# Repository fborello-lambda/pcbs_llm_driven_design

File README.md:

<div align="center">

# [pcbs_llm_driven_design](https://github.com/fborello-lambda/pcbs_llm_driven_design)

Four KiCad 10 hardware projects developed through an LLM-assisted design workflow.

Schematics · routed PCBs · readable BOMs · 3D previews · reproducible fabrication exports

</div>

| Board | Preview | Design files |
| --- | --- | --- |
| [220 Vac halogen dimmer](dimmer/) |  | [KiCad project](dimmer/esp32_dimmer.kicad_pro) · [schematic PDF](dimmer/docs/schematic.pdf) · [BOM](dimmer/docs/BOM.csv) |
| [BLE remote controller](remote_controller/) |  | [KiCad project](remote_controller/esp32c3_remote.kicad_pro) · [schematic PDF](remote_controller/docs/schematic.pdf) · [BOM](remote_controller/BOM.csv) |
| [Photodiode TIA laboratory](photodiode_lab/) |  | [KiCad project](photodiode_lab/photodiode_lab.kicad_pro) · [schematic PDF](photodiode_lab/docs/schematic.pdf) · [BOM](photodiode_lab/BOM.csv) |
| [Raspberry Pi SPI0 breakout](raspberry_spi0_breakout/) |  | [KiCad project](raspberry_spi0_breakout/raspberry_spi0_breakout.kicad_pro) · [schematic PDF](raspberry_spi0_breakout/docs/schematic.pdf) · [BOM](raspberry_spi0_breakout/BOM.csv) |

## Fabricated board photos

| Halogen dimmer | BLE remote controller | Photodiode TIA lab | Raspberry Pi SPI0 breakout |
| --- | --- | --- | --- |
|  |  |  |  |

## Repository layout

Each board has one self-contained project directory. Reusable ESP32-C3 symbol, footprint, and STEP assets live in `shared/`; deterministic generators and validation tools live in `scripts/`. Personal KiCad state, editor settings, caches, credentials, reports, and temporary files are excluded from version control.

The three ESP32 boards consume the same canonical ESP32-C3 SuperMini library. The Raspberry Pi board is an independent passive SPI0 adapter.

## Validation

Create the Python environment with access to KiCad's system-provided `pcbnew` module, then run the repository checks:

```sh
uv venv --python /usr/bin/python3 --system-site-packages
uv sync
uv run --no-sync python scripts/check_all.py
```

The check runs ERC, DRC, and schematic/PCB parity for all four projects. It also verifies the shared ESP32 footprint geometry and STEP reference on the three ESP32 boards.

Regenerate the committed documentation assets with:

```sh
uv run --no-sync python scripts/export_publishable_docs.py
```

## Fabrication ZIPs

Generate deterministic Gerber/drill ZIPs for all four boards with:

```sh
uv run --no-sync python scripts/export_fabrication.py
```

The ZIPs are written under each project's ignored `outputs/` directory. Publish tested ZIPs as GitHub Release assets so generated manufacturing files do not obscure source review or become stale in the main branch.

## Safety

These boards are engineering prototypes, not certified products. In particular, the dimmer switches 220 Vac and requires qualified review of creepage, clearance, insulation, fuse coordination, connector ratings, thermal performance, enclosure, EMC, and fabrication constraints before use. CAD checks do not establish electrical safety or the advertised load rating.

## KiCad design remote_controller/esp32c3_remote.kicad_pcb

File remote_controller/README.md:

# ESP32-C3 BLE dimmer remote — revision G

[KiCad project](esp32c3_remote.kicad_pro) · [Schematic PDF](docs/schematic.pdf) · [BOM CSV](BOM.csv)

Revision G is a 40 x 100 mm, 0.8 mm, two-layer controller for the dimmer. The ESP32-C3 SuperMini is directly soldered to the shared `Shared:ESP32-C3-SuperMini` SMD landing-pad footprint; there are no socket strips. A direct-solder Adafruit 2765 Mini Thumbstick controls brightness, three tactile buttons provide ON/SELECT, OFF/BACK, and PRESET, and a small I2C OLED reports state. There is no LDR in this revision.

The generated placement is portrait. The rear MPD BK-18650-PC2 holder is centred at x=20 mm, with its positive terminal at y=2.5 mm and its negative terminal at y=75.4 mm; the holder body ends at y=77.23 mm. The front OLED header starts at (16.19, 9.5) mm and reads VCC, GND, SCL, SDA from the front. The OLED support holes are at (8.35, 33.8) and (31.65, 33.8) mm. Button centres are x=8, 20, 32 mm at y=40 mm. The joystick centre is (20, 55.5) mm. The ESP32 footprint is at (13.5, 90) mm, rotated 90 degrees. Its USB faces outward through the left edge, with the connector mouth 0.5 mm inside the edge. The complete module is inside the 40 x 100 mm board. The four corner mounting holes were removed and the corner radius is 4 mm. Only the two OLED support holes remain.

The holder footprint uses an intentionally elevated terminal courtyard. Install a rigid insulating spacer with adhesive, with a total assembled thickness of 1.5 mm between the rear holder and the 0.8 mm PCB. Keep THT tails at or below 0.9 mm behind the holder: the MPD lead is 3.3 +/- 0.5 mm and the PCB is 0.8 mm, leaving at least 0.5 mm lead protrusion after the spacer. The holder screw locations are fabrication marks only, without carrier holes: attach it using the insulating spacer and adhesive. Cut recesses/windows in the spacer wherever solder tails occur; a solid sheet must not press on solder joints. C1 is at the front upper-left corner and JP1 at the front upper-right corner. BT1 is the only component fitted on the rear. The side-facing USB no longer requires an internal cable channel. The holder model and envelope are mechanical references; validate the purchased parts in a prototype. MPD source: [BK-18650-PC2 datasheet](https://www.batteryholders.com/uploads/parts/BK-18650-PC2/datasheets/BK-18650-PC2-datasheet.pdf).

## Electrical configuration

| Function | Revision G connection |
| --- | --- |
| Joystick X and Y | Adafruit 2765, with 10 kOhm / 22 kOhm dividers to 2.27 V full scale; ADC GPIO0 and GPIO1 |
| Battery measurement | VBUS/2 divider to GPIO3 |
| Buttons | ON/SELECT GPIO10, OFF/BACK GPIO20, PRESET GPIO21; internal pull-ups, switches to GND |
| OLED I2C | GPIO6 SDA and GPIO7 SCL; use the module's I2C pull-ups |
| Battery path | 18650 -> SW1 -> VBUS; onboard ME6211 supplies 3.3 V |

The single 18650 is externally charged. The SuperMini has no charger and the remote has no charge circuit. Its ME6211 dropout voltage limits useful operation from an 18650 as the cell discharges, so validate low-voltage behaviour with the actual SuperMini. USB and battery are manually isolated: turn the battery switch OFF and leave JP1 open before connecting USB. This is an assembly procedure, not automatic protection; the onboard diode does not isolate a battery sharing USB VBUS. A protected cell must be charged externally with a suitable charger.

Test firmware in Rust that draws the thumbstick position and button states on the OLED is in [`firmware/`](firmware/README.md).

## OLED and carrier

The specified display is the 0.96-inch SSD1306 reference module LCDWiki MC096VW/MC096VX, approximately 27.3 x 27.8 mm. Mechanical references: [LCDWiki MC096VX](https://www.lcdwiki.com/0.96inch_OLED_Module_(IIC-4P_SKU:MC096VX)) and [MC096-015 drawing](https://www.lcdwiki.com/images/1/19/MC096-015.jpg). The detailed selection and assembly notes are in [`OLED_SELECTION.md`](OLED_SELECTION.md).

With the display viewed from the front and its header at the top, the 2.54 mm pitch pins read left to right: VCC, GND, SCL, SDA. The carrier has a female socket on its front. Solder the straight male OLED header from the display front so the pins point rearward, then plug the OLED into the carrier. Solder the carrier socket from the back before installing the battery; the display remains removable. Use a low-profile OLED M2 rear head (head height <=1 mm) and two insulating M2 spacers; the nominal module underside is approximately 9.2 mm above the footprint plane. Verify the actual module and pin order before fabrication because generic modules can reverse VCC/GND. **The SSD1306 module used for the first build is GND, VDD, SCK, SDA, with the power pins swapped relative to J1. Do not plug it in directly; see [`LESSONS.md`](LESSONS.md).**

The joystick footprint is the official Adafruit 2765 Eagle geometry copied from `sources/adafruit-thumbstick.brd`; the applicable source license is in `sources/adafruit-license.txt`. The 3D joystick, holder, and OLED models are approximate envelopes for enclosure work. The elevated holder courtyard, terminal islands and full-body Fab model are intentional documentation for fabrication review; they are not a claim of factory-ready mechanical validation. ERC, DRC and schematic-to-PCB parity checks pass. Mechanical fit, battery operation and radio range still require a physical prototype.

The rear artwork is the photo-derived `art/argentina_hornero.svg` hornero and nest illustration with the visible caption `HORNERO`. Its reference and CC BY-SA 4.0 attribution are recorded in [`art/argentina_hornero_source.txt`](art/argentina_hornero_source.txt). The artwork and finishing tools under `scripts/remote_controller/` crop it to the exposed bottom rear and convert it to B.Silkscreen graphics (no copper), clipping ink away from pads.

## Build and assembly sequence

Run the project scripts in this order from the repository root:

```sh
uv run --no-sync python scripts/remote_controller/build_remote.py
uv run --no-sync python scripts/remote_controller/route_board.py
kicad-cli sch export netlist remote_controller/esp32c3_remote.kicad_sch --format kicadxml -o remote_controller/outputs/netlist.xml
uv run --no-sync python scripts/remote_controller/finish_remote.py
kicad-cli sch erc remote_controller/esp32c3_remote.kicad_sch --exit-code-violations -o remote_controller/outputs/erc.rpt
kicad-cli pcb drc remote_controller/esp32c3_remote.kicad_pcb --schematic-parity --exit-code-violations -o remote_controller/outputs/drc.rpt
```

The build tool regenerates the schematic, board, local libraries, BOM, and connectivity data. The routing tool routes the generated board. The finishing tool adds the approximate mechanical envelopes, crops the rear artwork, and performs source-geometry and connectivity checks. Always regenerate `outputs/netlist.xml` before the finishing step.

For assembly, fit the two insulating OLED M2 spacers and low-profile rear heads, solder the front OLED carrier, and keep the OLED removable. Install the rear holder on the 1.5 mm insulating spacer or adhesive pads; trim or select THT tails so no more than 0.9 mm protrudes behind it. Keep C1 and JP1 outside the holder body. Do not use holder screws in the USB plug overlap channel. Confirm battery polarity, cell length, OLED pin order, spacer and head heights, switch operation, antenna/USB clearance, and the USB isolation procedure on actual parts before applying power. Review the generated reports under `outputs/`; they are not a substitute for prototype hardware validation, firmware checks, battery testing, or radio-range testing.

The dimmer board in the repository root is a separate design. In revision G the complete ESP32 module stays inside the 40 x 100 mm PCB outline, with its USB connector facing the left edge.

## Revision G radio clearance

The antenna occupies the right end of the horizontal ESP32 module. Copper and vias are prohibited in x=24.2..40 mm, y=79.5..100 mm, on both copper layers. The rear battery holder ends at y=77.23 mm, so it does not overlap this area. Its approximately 2.27 mm gap is compact and does not provide a generous RF metal clearance. Measure BLE range with the actual cell, enclosure and hand grip; the drawing and DRC cannot establish antenna performance.

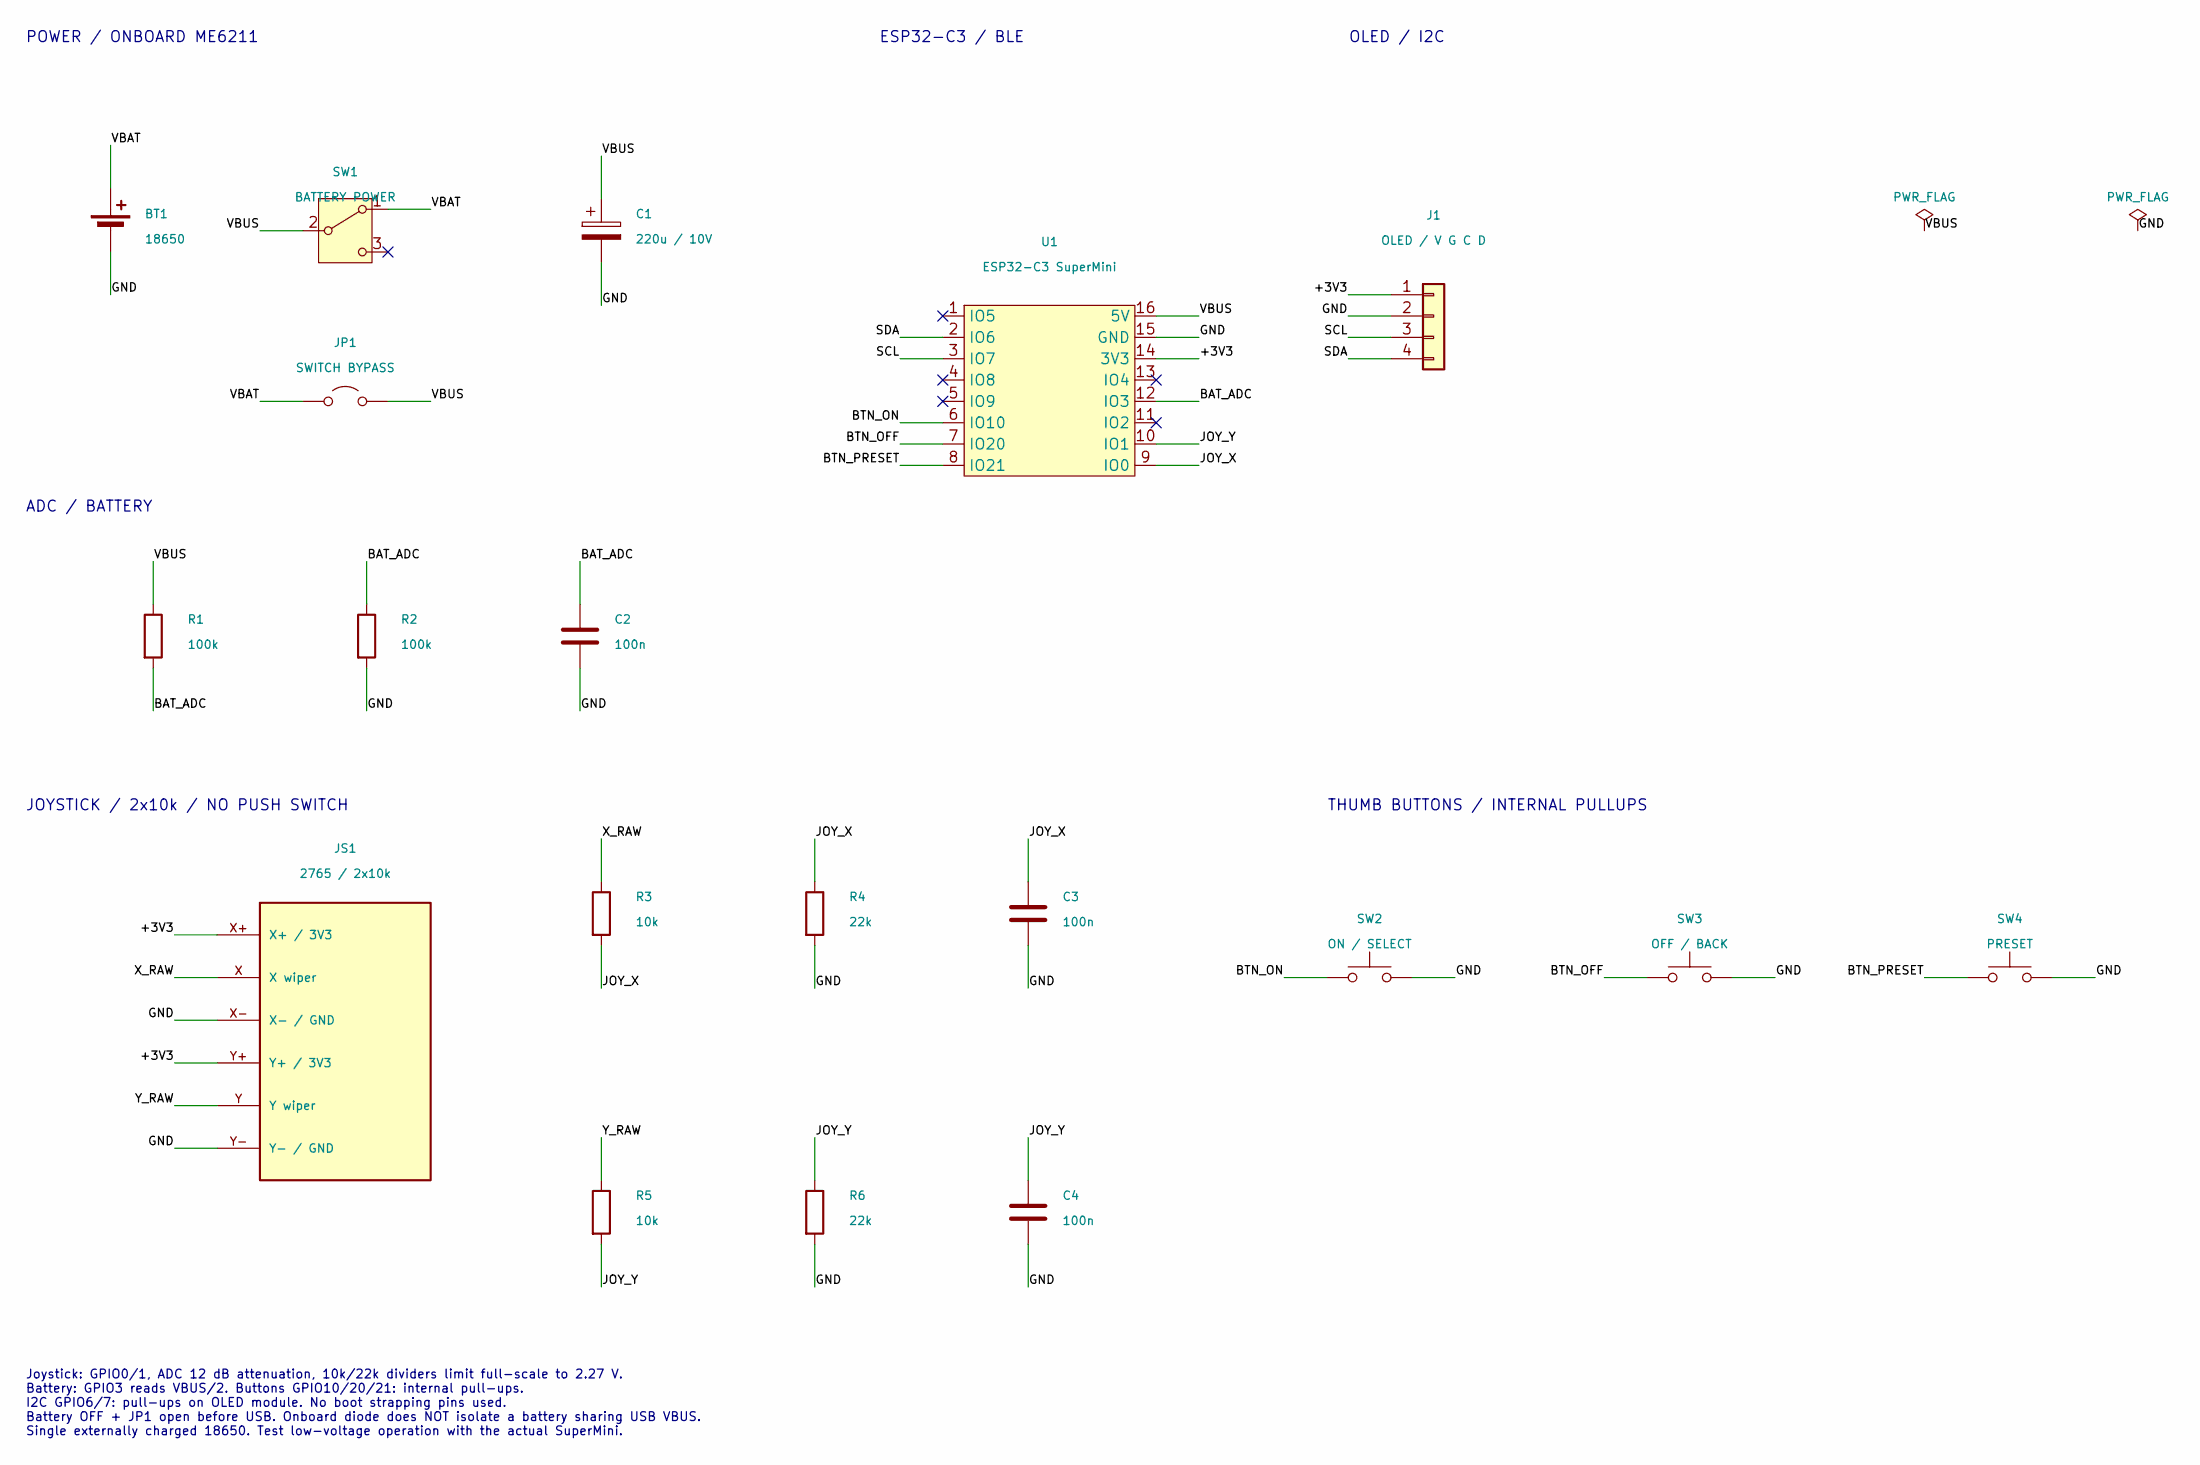
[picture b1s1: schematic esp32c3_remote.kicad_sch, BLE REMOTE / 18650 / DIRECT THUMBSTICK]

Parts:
BT1: 18650; BT1
C1: 220u / 10V; C1
C2: 100n; C2
C3: 100n; C3
C4: 100n; C4
J1: OLED / V G C D; J1
JP1: SWITCH BYPASS; JP1
JS1: 2765 / 2x10k; JS1
R1: 100k; R1
R2: 100k; R2
R3: 10k; R3
R4: 22k; R4
R5: 10k; R5
R6: 22k; R6
SW1: BATTERY POWER; SW1
SW2: ON / SELECT; SW2
SW3: OFF / BACK; SW3
SW4: PRESET; SW4
U1: ESP32-C3 SuperMini; ESP32-C3-SuperMini

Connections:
/+3V3: J1.1, JS1.X+ (X+ / 3V3), JS1.Y+ (Y+ / 3V3), U1.14 (3V3)
/BAT_ADC: C2.1, R1.2, R2.1, U1.12 (IO3)
/BTN_OFF: SW3.1, U1.7 (IO20)
/BTN_ON: SW2.1, U1.6 (IO10)
/BTN_PRESET: SW4.1, U1.8 (IO21)
/GND: BT1.2 (-), C1.2, C2.2, C3.2, C4.2, J1.2, JS1.X- (X- / GND), JS1.Y- (Y- / GND), R2.2, R4.2, R6.2, SW2.2, SW3.2, SW4.2, U1.15 (GND)
/JOY_X: C3.1, R3.2, R4.1, U1.9 (IO0)
/JOY_Y: C4.1, R5.2, R6.1, U1.10 (IO1)
/SCL: J1.3, U1.3 (IO7)
/SDA: J1.4, U1.2 (IO6)
/VBAT: BT1.1 (+), JP1.1 (A), SW1.1 (A)
/VBUS: C1.1, JP1.2 (B), R1.1, SW1.2 (B), U1.16 (5V)
/X_RAW: JS1.X (X wiper), R3.1
/Y_RAW: JS1.Y (Y wiper), R5.1

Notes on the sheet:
POWER / ONBOARD ME6211
ESP32-C3 / BLE
OLED / I2C
ADC / BATTERY
JOYSTICK / 2x10k / NO PUSH SWITCH
THUMB BUTTONS / INTERNAL PULLUPS
Joystick: GPIO0/1, ADC 12 dB attenuation, 10k/22k dividers limit full-scale to 2.27 V. Battery: GPIO3 reads VBUS/2. Buttons GPIO10/20/21: internal pull-ups. I2C GPIO6/7: pull-ups on OLED module. No boot strapping pins used. Battery OFF + JP1 open before USB. Onboard diode does NOT isolate a battery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

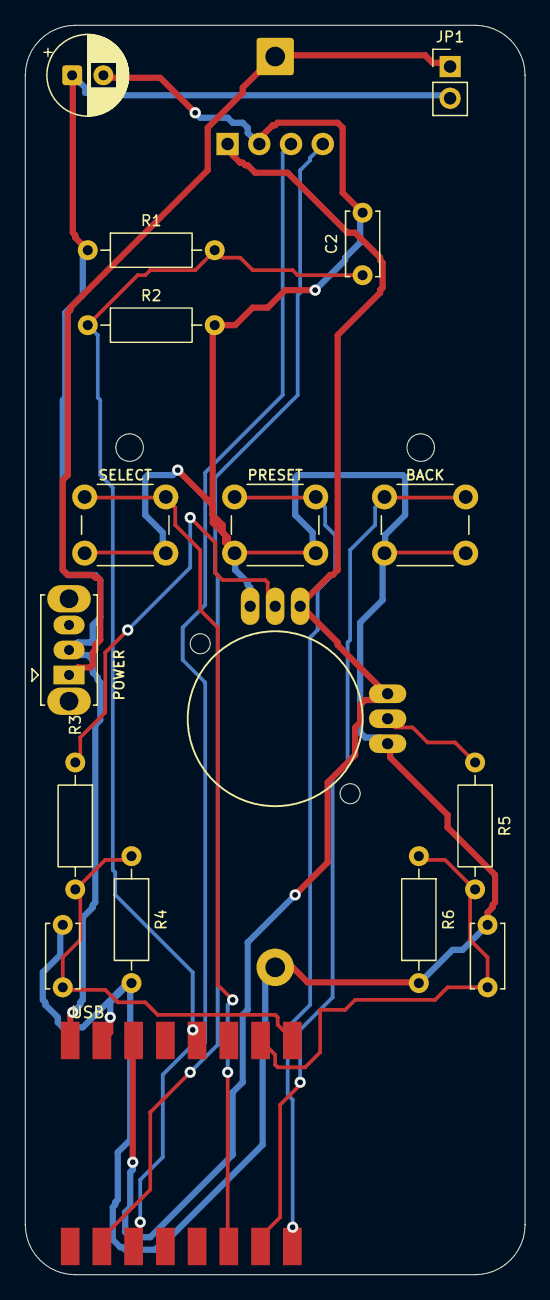
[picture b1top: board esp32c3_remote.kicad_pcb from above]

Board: 2 copper layers, 40.0 x 100.0 mm, 21 parts (1 on the bottom side), 14 nets.

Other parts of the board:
H5, H6: MountingHole_2.2mm_M2

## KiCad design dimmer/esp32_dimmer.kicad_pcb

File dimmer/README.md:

# ESP32-C3 220 Vac halogen dimmer

Two-layer 100 x 100 mm phase-control dimmer for a nominal 220 Vac, 50 Hz, 1000 W halogen load. An external SELV 3.3 V I2C connection powers the ESP32-C3 SuperMini. A MOC3052M provides random-phase optical triggering, an H11AA1 detects zero crossings, and a BTA16-800BW switches the load.

## Files

- [KiCad project](esp32_dimmer.kicad_pro)
- [Schematic PDF](docs/schematic.pdf)
- [BOM CSV](docs/BOM.csv)
- [Revision notes](docs/REVISION_J.md)
- [Zero-cross calculations](docs/ZERO_CROSS_CALCULATION.md)
- [Design calculations](docs/DESIGN_CALCULATIONS.md)
- [Fabrication requirements](docs/PCB_FABRICATION.md)
- [Firmware, bring-up and testing](firmware/README.md)
- [Firmware debugging notes](firmware/DEBUGGING_NOTES.md)

## Safety

This board switches lethal mains voltage and is not certified. It must not be treated as safe solely because ERC and DRC pass. Preserve the isolation slot and explicit MAINS/SELV constraints, and independently review creepage, clearance, fuse coordination, thermal performance, component ratings, enclosure, and fabrication capability before energizing it.

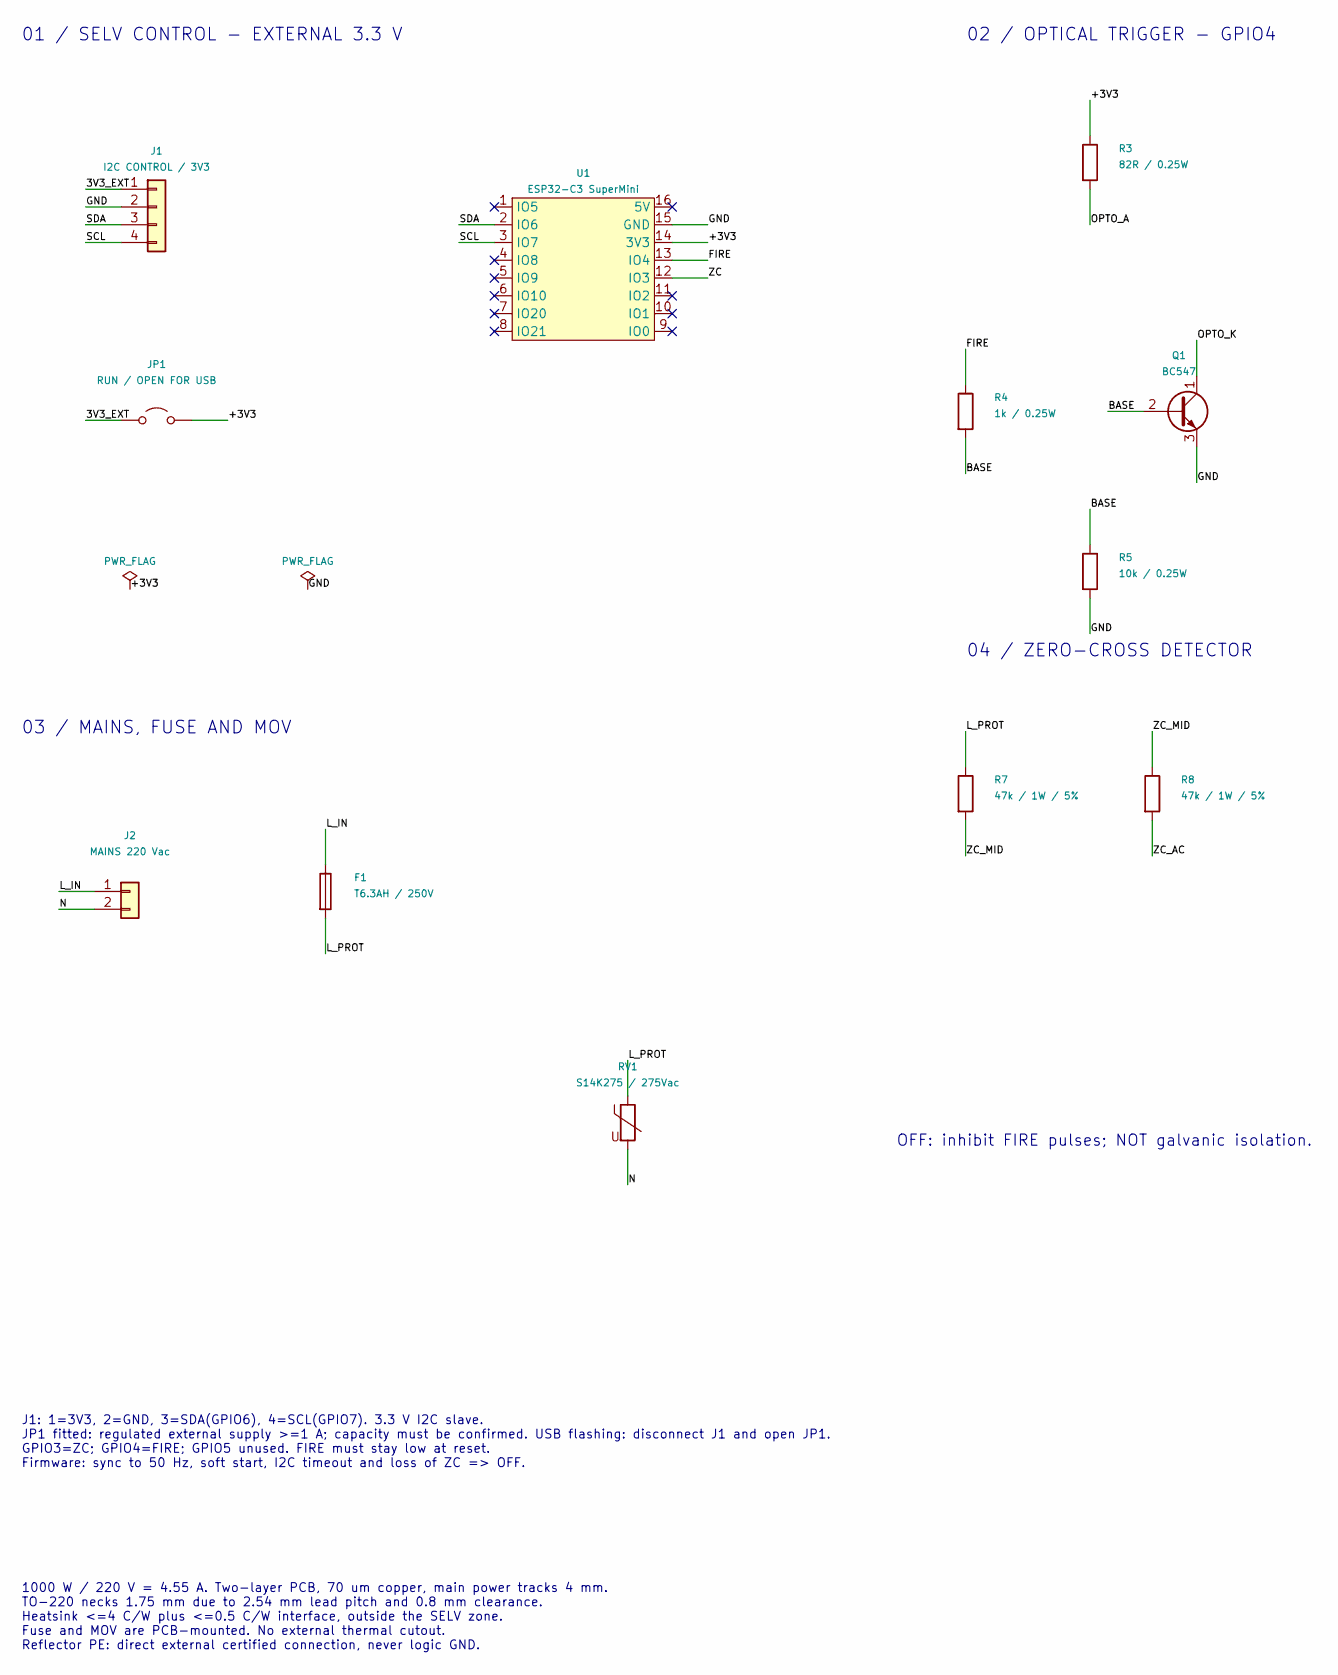
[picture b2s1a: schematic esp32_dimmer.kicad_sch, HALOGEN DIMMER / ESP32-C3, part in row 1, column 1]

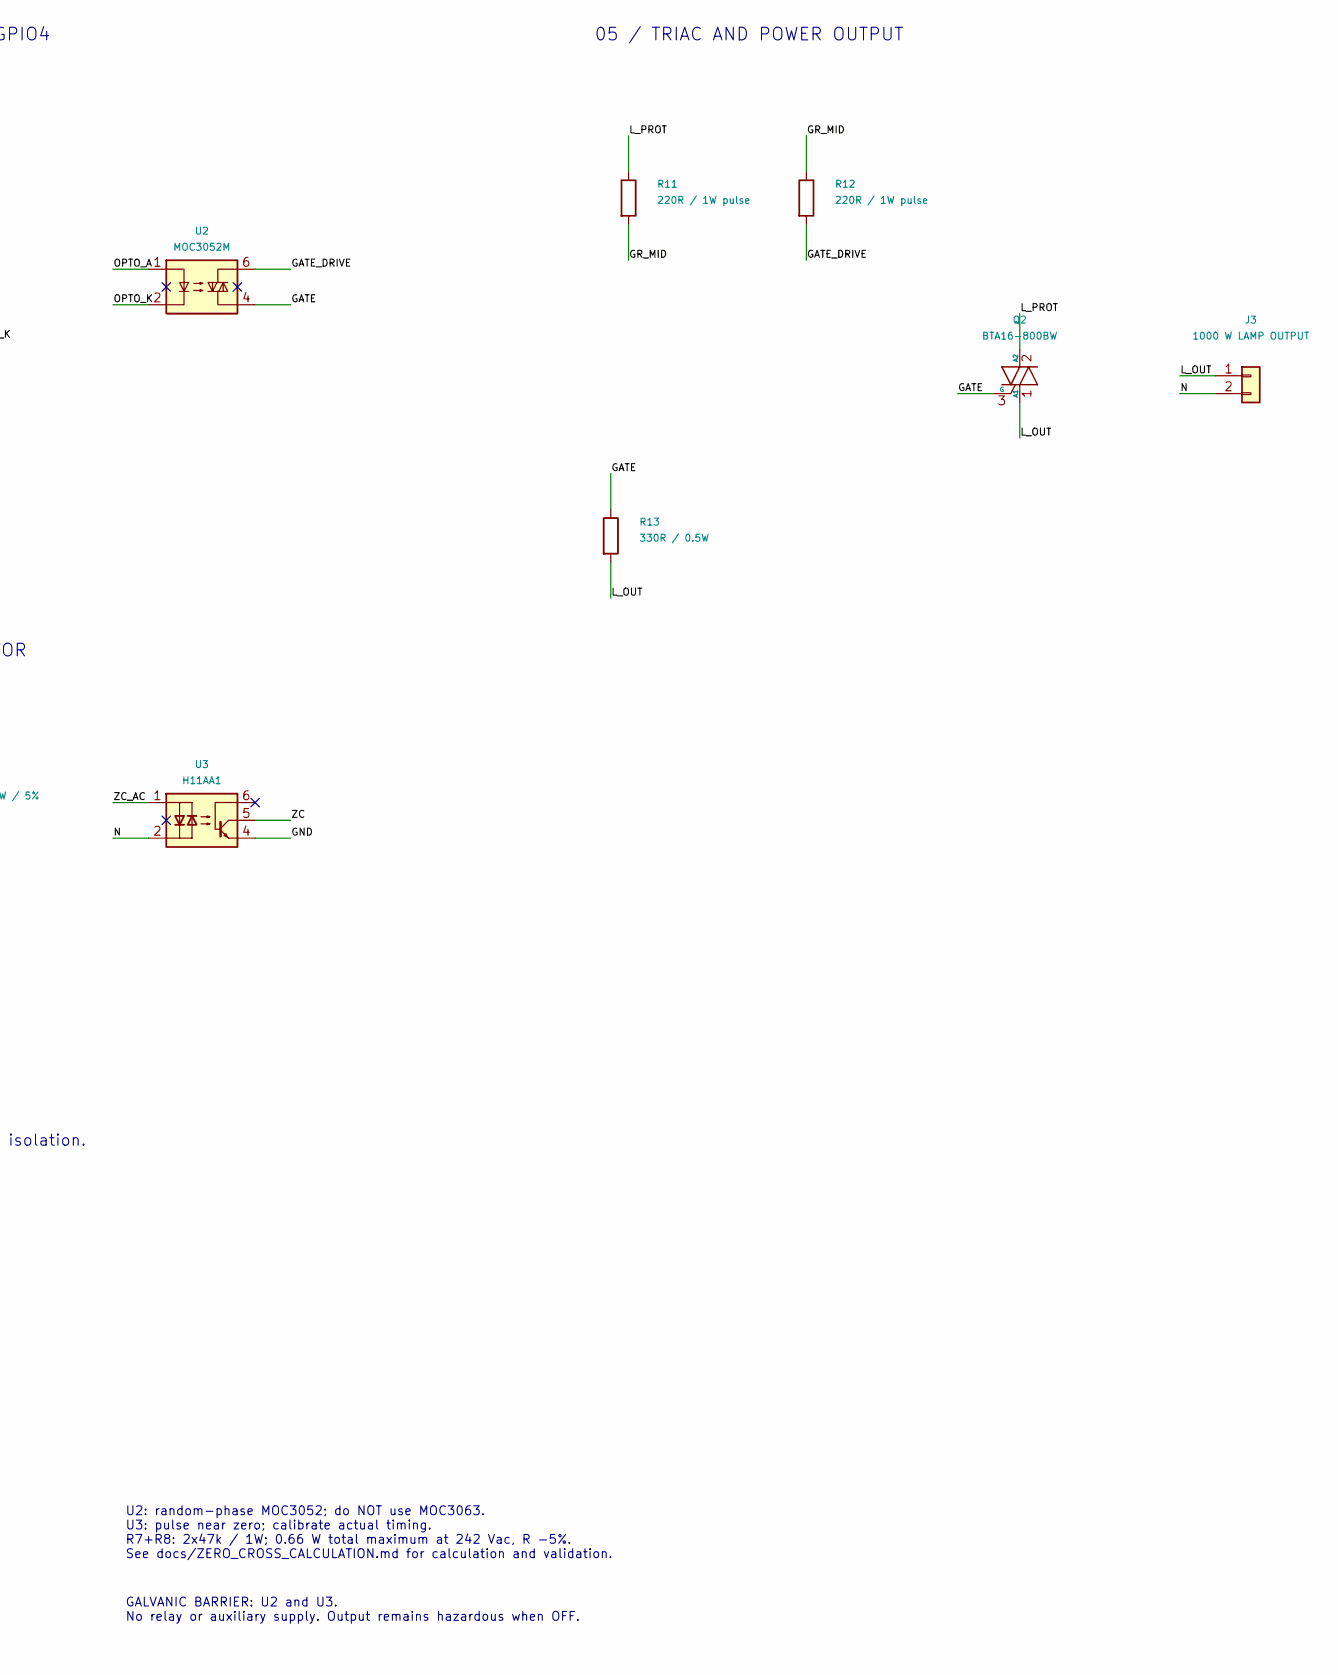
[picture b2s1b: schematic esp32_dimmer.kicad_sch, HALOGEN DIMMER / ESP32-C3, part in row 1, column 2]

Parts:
F1: T6.3AH / 250V; F1_Fuseholder_Conquer_CQ-200S_P23.50mm
J1: I2C CONTROL / 3V3; J1_JST_XH_B4B-XH-A_1x04_P2.50mm_Vertical
J2: MAINS 220 Vac; J2_Wuerth_691311400102_P7.62mm
J3: 1000 W LAMP OUTPUT; J3_Wuerth_691311400102_P7.62mm
JP1: RUN / OPEN FOR USB; JP1_PinHeader_1x02_P2.54mm_Vertical
Q1: BC547; Q1_TO-92_Inline_Wide
Q2: BTA16-800BW; Q2_TO-220-3_Vertical
R3: 82R / 0.25W; R3_R_Axial_DIN0207_L6.3mm_D2.5mm_P10.16mm_Horizontal
R4: 1k / 0.25W; R4_R_Axial_DIN0207_L6.3mm_D2.5mm_P10.16mm_Horizontal
R5: 10k / 0.25W; R5_R_Axial_DIN0207_L6.3mm_D2.5mm_P10.16mm_Horizontal
R7: 47k / 1W / 5%; R7_R_Axial_DIN0414_L11.9mm_D4.5mm_P20.32mm_Horizontal
R8: 47k / 1W / 5%; R8_R_Axial_DIN0414_L11.9mm_D4.5mm_P20.32mm_Horizontal
R11: 220R / 1W pulse; R11_R_Axial_DIN0414_L11.9mm_D4.5mm_P20.32mm_Horizontal
R12: 220R / 1W pulse; R12_R_Axial_DIN0414_L11.9mm_D4.5mm_P20.32mm_Horizontal
R13: 330R / 0.5W; R13_R_Axial_DIN0309_L9.0mm_D3.2mm_P12.70mm_Horizontal
RV1: S14K275 / 275Vac; RV1_RV_Disc_D15.5mm_W5mm_P7.5mm
U1: ESP32-C3 SuperMini; ESP32-C3-SuperMini
U2: MOC3052M; U2_DIP-6_W10.16mm
U3: H11AA1; U3_DIP-6_W10.16mm

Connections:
/3V3_EXT: J1.1, JP1.1 (A)
/+3V3: JP1.2 (B), R3.1, U1.14 (3V3)
/BASE: Q1.2 (B), R4.2, R5.1
/FIRE: R4.1, U1.13 (IO4)
/GATE: Q2.3 (G), R13.1, U2.4
/GATE_DRIVE: R12.2, U2.6
/GND: J1.2, Q1.3 (E), R5.2, U1.15 (GND), U3.4
/GR_MID: R11.2, R12.1
/L_IN: F1.1, J2.1
/L_OUT: J3.1, Q2.1 (A1), R13.2
/L_PROT: F1.2, Q2.2 (A2), R7.1, R11.1, RV1.1
/N: J2.2, J3.2, RV1.2, U3.2
/OPTO_A: R3.2, U2.1
/OPTO_K: Q1.1 (C), U2.2
/SCL: J1.4, U1.3 (IO7)
/SDA: J1.3, U1.2 (IO6)
/ZC: U1.12 (IO3), U3.5
/ZC_AC: R8.2, U3.1
/ZC_MID: R7.2, R8.1

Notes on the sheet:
01 / SELV CONTROL - EXTERNAL 3.3 V
02 / OPTICAL TRIGGER - GPIO4
03 / MAINS, FUSE AND MOV
04 / ZERO-CROSS DETECTOR
05 / TRIAC AND POWER OUTPUT
OFF: inhibit FIRE pulses; NOT galvanic isolation.
GALVANIC BARRIER: U2 and U3. No relay or auxiliary supply. Output remains hazardous when OFF.
J1: 1=3V3, 2=GND, 3=SDA(GPIO6), 4=SCL(GPIO7). 3.3 V I2C slave. JP1 fitted: regulated external supply >=1 A; capacity must be confirmed. USB flashing: disconnect J1 and open JP1. GPIO3=ZC; GPIO4=FIRE; GPIO5 unused. FIRE must stay low at reset. Firmware: sync to 50 Hz, soft start, I2C timeout and los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
1000 W / 220 V = 4.55 A. Two-layer PCB, 70 um copper, main power tracks 4 mm. TO-220 necks 1.75 mm due to 2.54 mm lead pitch and 0.8 mm clearance. Heatsink <=4 C/W plus <=0.5 C/W interface, outside the SELV zone. Fuse and MOV are PCB-mounted. No external thermal cutout. Reflector PE: direct externa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
U2: random-phase MOC3052; do NOT use MOC3063. U3: pulse near zero; calibrate actual timing. R7+R8: 2x47k / 1W; 0.66 W total maximum at 242 Vac, R -5%. See docs/ZERO_CROSS_CALCULATION.md for calculation and validation.

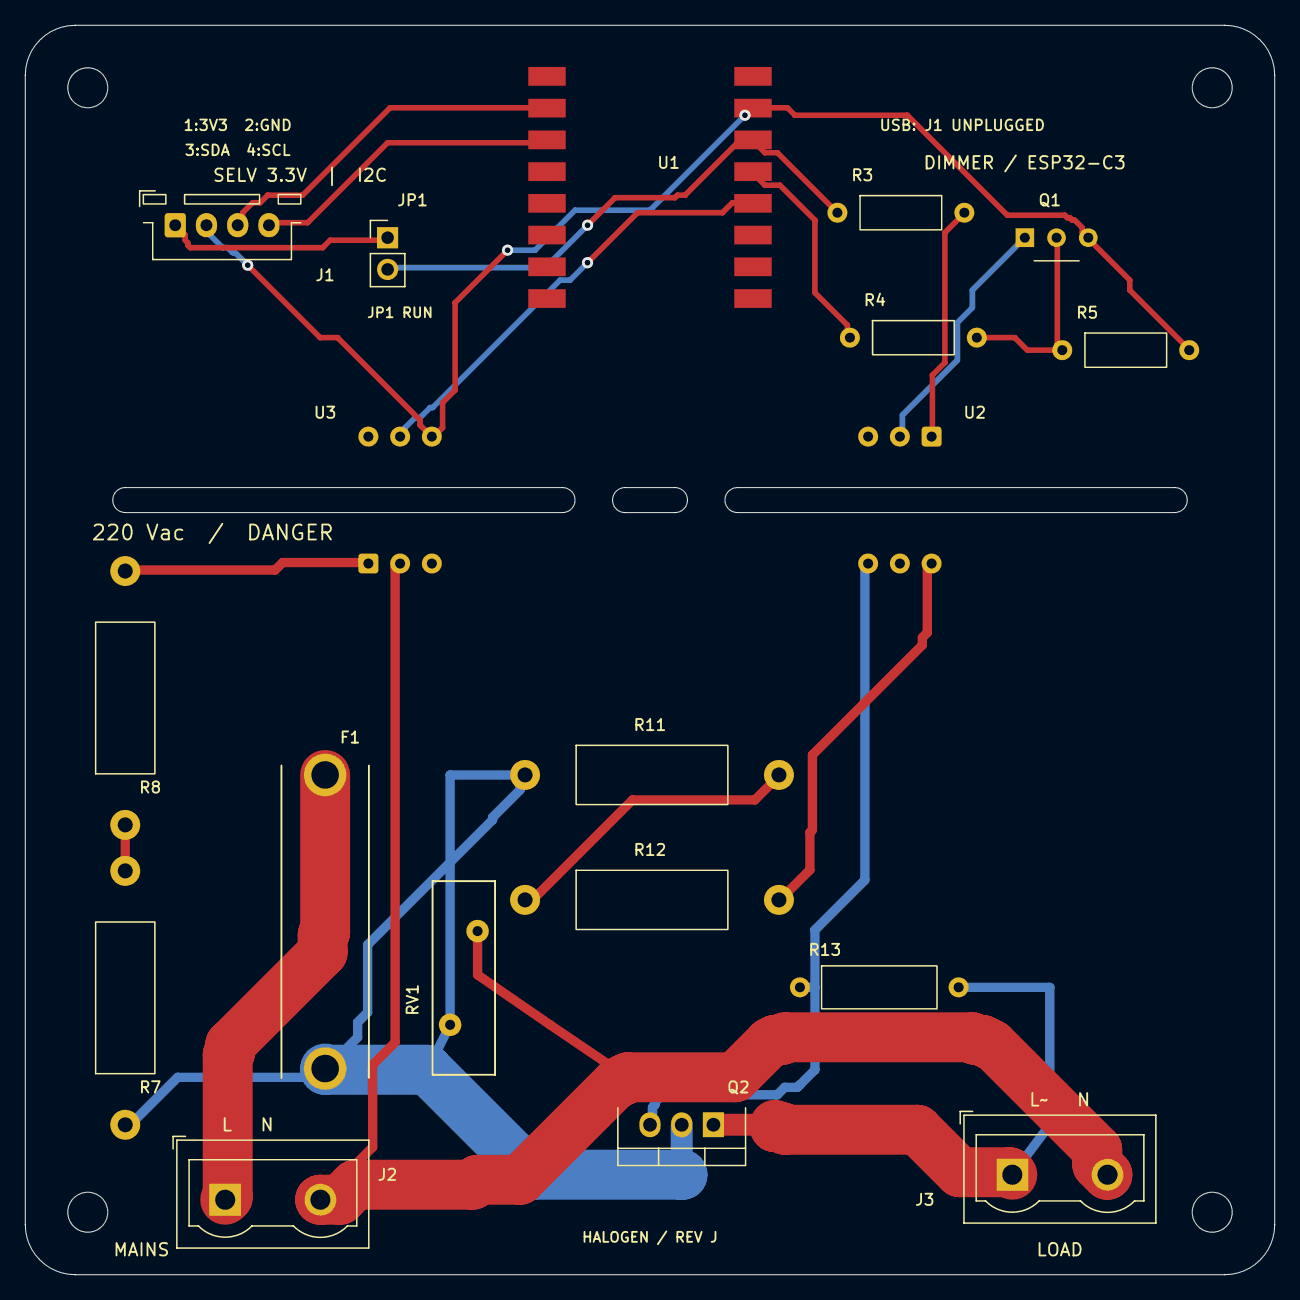
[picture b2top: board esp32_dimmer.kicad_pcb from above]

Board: 2 copper layers, 100.0 x 100.0 mm, 23 parts (0 on the bottom side), 19 nets.

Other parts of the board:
H1: MountingHole_3.2mm_M3; H1_MountingHole_3.2mm_M3
H2: MountingHole_3.2mm_M3; H2_MountingHole_3.2mm_M3
H3: MountingHole_3.2mm_M3; H3_MountingHole_3.2mm_M3
H4: MountingHole_3.2mm_M3; H4_MountingHole_3.2mm_M3

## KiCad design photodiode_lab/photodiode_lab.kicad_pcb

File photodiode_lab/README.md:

# Photodiode transimpedance lab — revision D

[KiCad project](photodiode_lab.kicad_pro) · [Schematic PDF](docs/schematic.pdf) · [BOM CSV](BOM.csv)

This is a 3.3 V teaching transimpedance amplifier (TIA) for a Vishay BPW34, an MCP6002-I/P in an 8-pin DIP socket, and the shared direct-solder ESP32-C3 footprint. The ESP32-C3 GPIO0 ADC input is `ADC_OUT`.

## Wiring and functional diagram

Fit the BPW34 in the marked top-view orientation: pad 1 (`K`, cathode) goes to the MCP6002 A inverting input, net `SUM`; pad 2 (anode) goes to `GND`. On the PCB, K is on the right and the anode on the left. The photodiode is therefore reverse biased at about 1.65 V. The MCP6002 DIP-8 pinout is: 1 OUTA=`VOUT`, 2 INA−=`SUM`, 3 INA+=`VREF`, 4 VSS=`GND`, 5 INB+=`REF_DIV`, 6 INB−=`VREF`, 7 OUTB=`VREF`, 8 VDD=`+3V3`.

R1/R2 make the 1.65 V divider and MCP6002 section B buffers it. RF1 is an ordinary soldered 100 kOhm, 1% axial resistor. CF1 is the fixed 1 nF C0G capacitor in parallel with RF1. Any future resistor variation is left to the user; power must be OFF before modifying the feedback components.

The front silkscreen integrates the functional A-channel TIA diagram with the actual BPW34, RF1, CF1, MCP6002, divider, and test-point locations. The diagram surrounds the real MCP6002 package, which contains both amplifier A and the VREF buffer B. Its printed lines depict functional connections and are not the physical DIP pin map.

## Theory and ranges

Before output clipping, `VOUT = VREF + IPH × RF1`; this polarity follows from the cathode-at-SUM and anode-at-ground connection. The feedback pole is `fc ≈ 1/(2π × RF1 × CF1)`. The fitted values remain documented in the schematic and BOM, while the front silkscreen uses reference designators so it remains correct if either component changes.

To choose R1/R2, RF1, R3/R4 and the ADC attenuation for a given light range, follow [docs/MEASUREMENT_RANGE.md](docs/MEASUREMENT_RANGE.md). The Rust firmware in [firmware/](firmware/README.md) serves a phone page with live readings, an attenuation selector and the same calculations.

The feedback pole `1/(2πRF·1 nF)` is about 15.9 kHz, 1.59 kHz, and 159 Hz for those three settings. The 1 nF capacitor is intentionally much larger than the BPW34's tens-of-pF junction capacitance, giving a slow, stable teaching response.

`ADC_OUT` is the divider midpoint: `VADC = VOUT × R4/(R3+R4)`, with R3 between VOUT and ADC and R4 between ADC and GND. The fitted values R3=10 kOhm and R4=22 kOhm give a factor of 0.6875. C4 forms a low-pass with R3 in parallel with R4: `fc ≈ 1/[2π × (R3 || R4) × C4]`, approximately 232 Hz with the fitted values. Recalculate ADC headroom and filtering if either resistor changes. Calibrate the ESP32 ADC and dark offset; the ADC voltage increases with light.

## Test points and references

The actual front test-point locations are TP1=`VOUT` at (78, 60) mm, TP2=`VREF` at (29, 69) mm, TP3=`ADC_OUT` at (88, 78.16) mm, and TP4=`GND` at (88, 93.16) mm. Keep the sensitive `SUM` node short and avoid probing it during normal measurements. Revision D has no rear theory artwork; the functional diagram is on the front around the actual parts.

Primary references: [Vishay BPW34 datasheet](https://www.vishay.com/docs/81521/bpw34.pdf) and [Microchip MCP6002 datasheet](https://ww1.microchip.com/downloads/en/DeviceDoc/MCP6001-1R-1U-2-4-1-MHz-Low-Power-Op-Amp-DS20001733L.pdf).

## CAD and checks

The two-layer PCB is 100 x 100 mm with rounded corners and four M3 clearance holes. Fit the MCP6002 in U2's DIP-8 socket, matching the notch. D1's square pad is cathode K. The photodiode and other 3D renders are approximate envelopes; inspect the purchased parts before fabrication.

Rebuild from the repository root with the uv environment described in the root README:

```sh
uv run --no-sync python scripts/photodiode_lab/build_lab.py
uv run --no-sync python scripts/photodiode_lab/route_board.py
kicad-cli sch export netlist photodiode_lab/photodiode_lab.kicad_sch --format kicadxml -o photodiode_lab/outputs/netlist.xml
uv run --no-sync python scripts/photodiode_lab/finish_lab.py
kicad-cli sch erc photodiode_lab/photodiode_lab.kicad_sch --exit-code-violations -o photodiode_lab/outputs/erc.rpt
kicad-cli pcb drc photodiode_lab/photodiode_lab.kicad_pcb --schematic-parity --exit-code-violations -o photodiode_lab/outputs/drc.rpt
```

Revision D passes ERC, DRC and schematic-to-PCB parity checks with no violations or unconnected items. Independent checks verify all 53 connected pins, BPW34 polarity, the MCP6002 pin map, and the exact dimmer ESP32 pad geometry. Prototype testing must establish noise, offset, stability, clipping, and usable light range. This is a prototype teaching board, not a calibrated light meter.

## Optional SMD soldering exercise

The top strip adds a static LED circuit, enabled by the normally open JP1 header. It shares only +3V3 and ground with the laboratory circuit; it has no connection to SUM, VREF or the ADC signal. The TIA works with the entire exercise unpopulated.

Solder in increasing difficulty: R5=1k (1206), R6=0 ohm (0805), R7=0 ohm (0603), and D2=red LED (0805, cathode on the right). R5 must remain 1k: it limits LED current to roughly 1-2mA at 3.3V. Pads A, B, C, D and GND are built-in copper test pads, not purchased components.

With USB disconnected and JP1 open, check approximately 1k between A and B, continuity from B through C to D, and inspect for solder bridges. Check LED polarity with diode mode. Then connect USB and fit the JP1 shunt: the LED should light without firmware. Measure V(A)-V(B) to estimate current using I=V/R5. Remove JP1 before photodiode measurements to avoid LED illumination influencing the sensor and to remove the practice load. A dark LED with JP1 fitted can indicate an open solder joint, reversed LED, missing component, or a supply problem. Never use continuity mode on the powered board.

Revision D: dark output is approximately 1.65 V, not zero. With RF1=100k, an additional 1uA of photocurrent raises VOUT by 100mV and ADC_OUT by 68.75mV before clipping. Calibrate the actual dark output, including ambient light and offset.

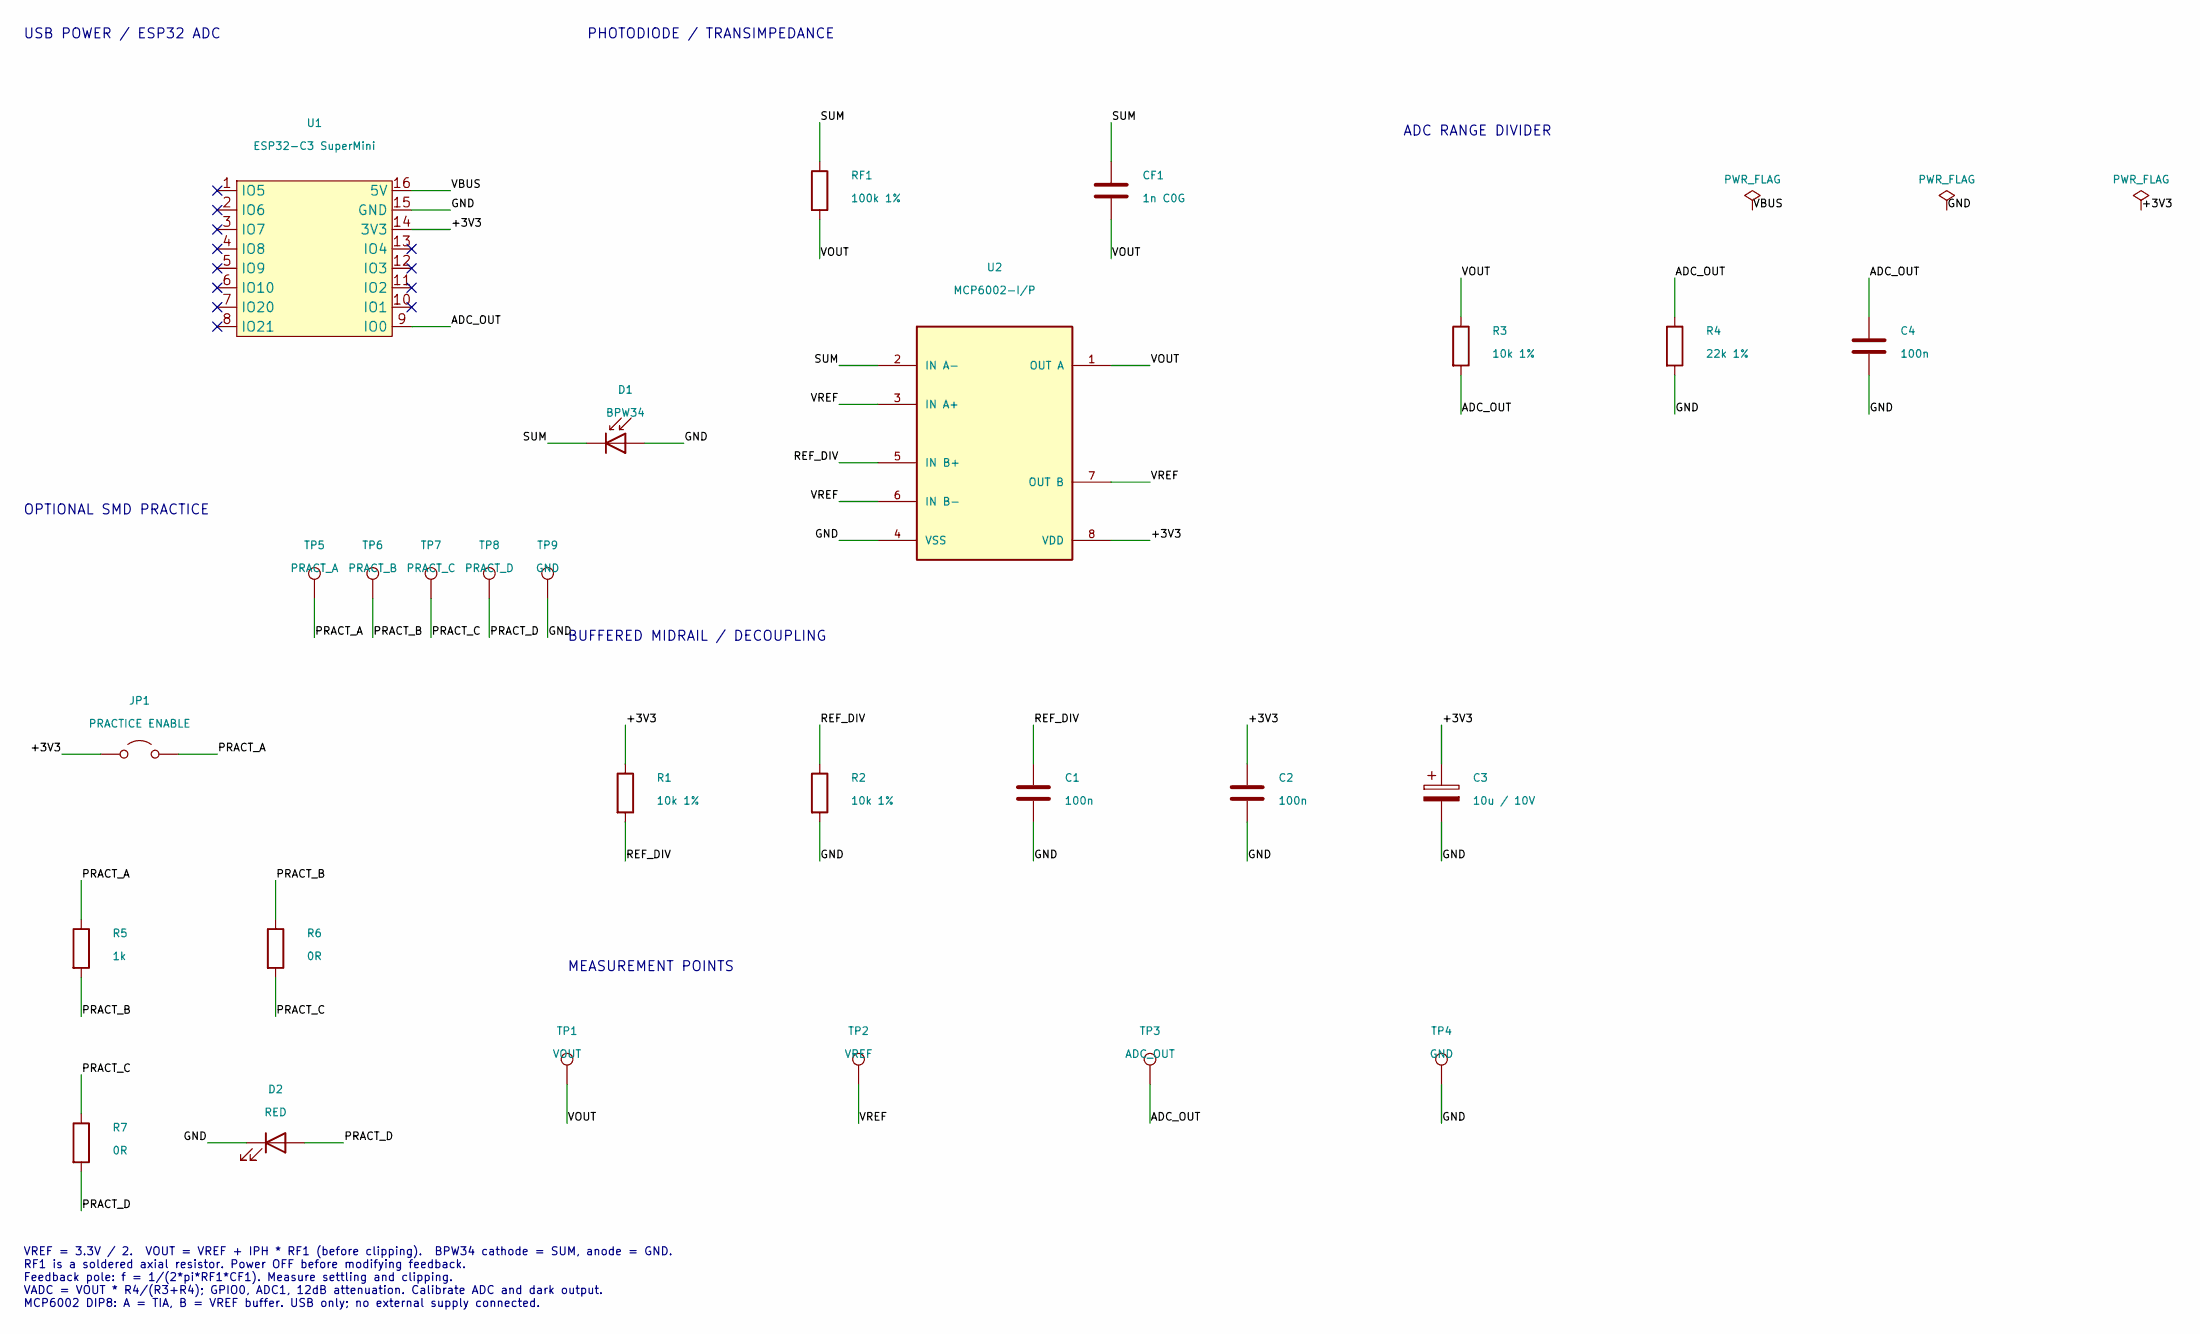
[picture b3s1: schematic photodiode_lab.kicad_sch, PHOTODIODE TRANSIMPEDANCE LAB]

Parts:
C1: 100n; C1
C2: 100n; C2
C3: 10u / 10V; C3
C4: 100n; C4
CF1: 1n C0G; CF1
D1: BPW34; D1
D2: RED; D2
JP1: PRACTICE ENABLE; JP1
R1: 10k 1%; R1
R2: 10k 1%; R2
R3: 10k 1%; R3
R4: 22k 1%; R4
R5: 1k; R5
R6: 0R; R6
R7: 0R; R7
RF1: 100k 1%; RF1
TP1: VOUT; TP1
TP2: VREF; TP2
TP3: ADC_OUT; TP3
TP4: GND; TP4
TP5: PRACT_A; TP5
TP6: PRACT_B; TP6
TP7: PRACT_C; TP7
TP8: PRACT_D; TP8
TP9: GND; TP9
U1: ESP32-C3 SuperMini; ESP32-C3-SuperMini
U2: MCP6002-I/P; U2

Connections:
/+3V3: C2.1, C3.1, JP1.1 (A), R1.1, U1.14 (3V3), U2.8 (VDD)
/ADC_OUT: C4.1, R3.2, R4.1, TP3.1, U1.9 (IO0)
/GND: C1.2, C2.2, C3.2, C4.2, D1.2 (A), D2.1 (K), R2.2, R4.2, TP4.1, TP9.1, U1.15 (GND), U2.4 (VSS)
/PRACT_A: JP1.2 (B), R5.1, TP5.1
/PRACT_B: R5.2, R6.1, TP6.1
/PRACT_C: R6.2, R7.1, TP7.1
/PRACT_D: D2.2 (A), R7.2, TP8.1
/REF_DIV: C1.1, R1.2, R2.1, U2.5 (IN B+)
/SUM: CF1.1, D1.1 (K), RF1.1, U2.2 (IN A-)
/VBUS: U1.16 (5V)
/VOUT: CF1.2, R3.1, RF1.2, TP1.1, U2.1 (OUT A)
/VREF: TP2.1, U2.3 (IN A+), U2.6 (IN B-), U2.7 (OUT B)

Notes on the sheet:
USB POWER / ESP32 ADC
PHOTODIODE / TRANSIMPEDANCE
ADC RANGE DIVIDER
BUFFERED MIDRAIL / DECOUPLING
MEASUREMENT POINTS
OPTIONAL SMD PRACTICE
VREF = 3.3V / 2. VOUT = VREF + IPH * RF1 (before clipping). BPW34 cathode = SUM, anode = GND. RF1 is a soldered axial resistor. Power OFF before modifying feedback. Feedback pole: f = 1/(2*pi*RF1*CF1). Measure settling and clipping. VADC = VOUT * R4/(R3+R4); GPIO0, ADC1, 12dB attenuation. Calibrate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
